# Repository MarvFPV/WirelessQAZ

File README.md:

# WARNING: Unsure if i ever fixed the electrical issues around the charging IC, please sanity check before using

# QAZ-BLE

a 34 key, QAZ style, integrated BLE keyboard.   
Included are PCB files and 3d printable case files.

### PCB
The PCB includes in-switch LED lighting, USB-C, ESD protection and battery protection, enabling the user to install pretty much any Lipo cell that will fit inside the case

### Case
Hardware needed:

* 8x m3x10mm countersinks
* 4x m3x8mm button head

Printing:

* Print from any non-flexible material, i'd recommend to keep the bottom case metal free for RF reasons tho i have no clue how much of an effect that'd have real world
* no real layer height restrictions, make sure that you can print the threads at least decently well
* 4 or more shells are recommended for a better sounding keyboard aswell as stronger threads
* infill does not matter apart from sound

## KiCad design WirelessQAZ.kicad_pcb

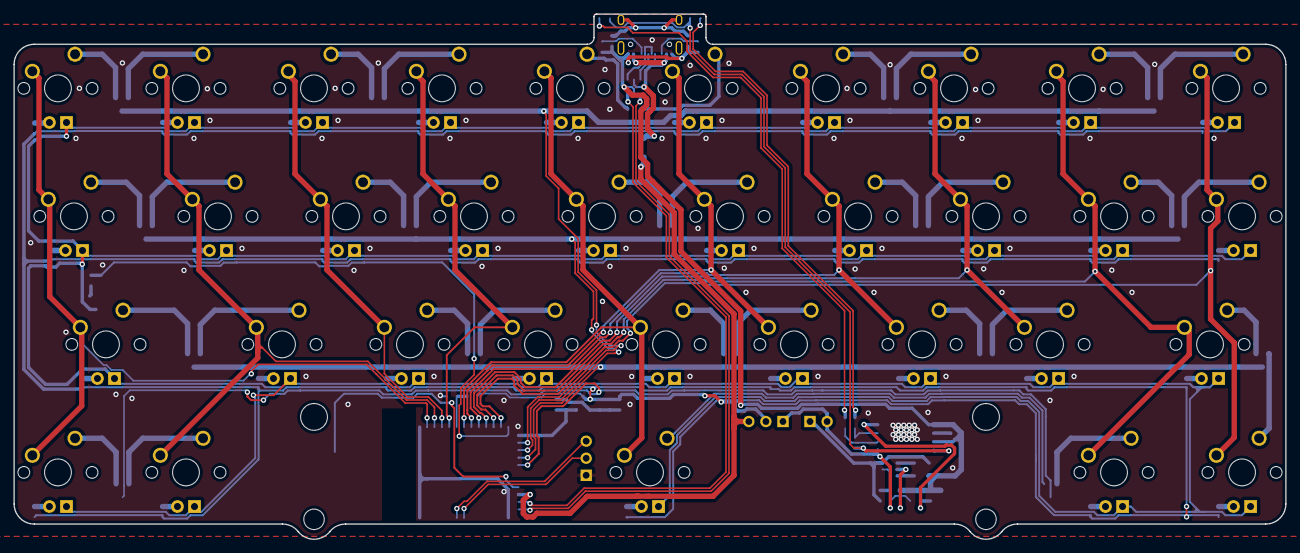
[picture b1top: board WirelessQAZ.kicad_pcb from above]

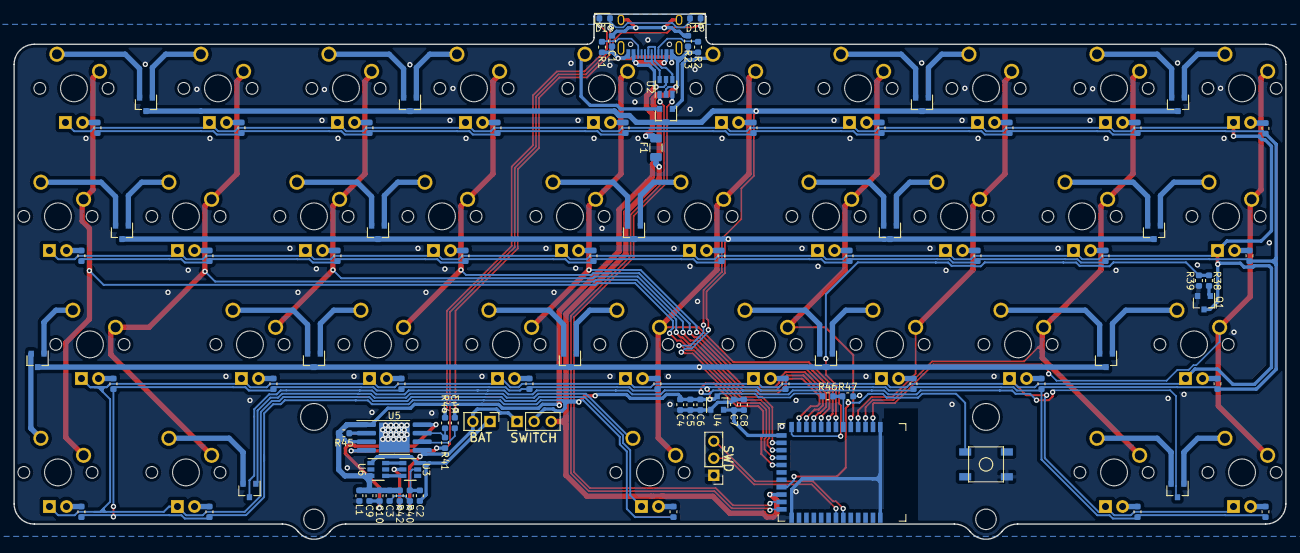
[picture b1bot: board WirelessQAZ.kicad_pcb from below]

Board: 2 copper layers, 189.3 x 78.1 mm, 124 parts (90 on the bottom side), 115 nets.

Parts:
BAT: BATT; PinHeader_1x02_P2.54mm_Vertical
C1, C2, C8, C10: 100nF; C_0603_1608Metric_stealth
C3, C9: 10uF; C_0603_1608Metric_stealth
C4, C5: 4.7uF; C_0603_1608Metric_stealth
C6, C7: 1uF; C_0603_1608Metric_stealth
D1, D2, D3, D4, D5, D6, D7, D8, D9, D10, D11, D12, D13, D14, D15, D16, D17: D_Schottky_x2_KCom_AAK; SOT-23
D18, D19: LED_Small; LED_0603_1608Metric
F1: 500mA; Fuse_1206_3216Metric
L1: PBY160808T-181Y-N; L_0603_1608Metric
MX1, MX2, MX3, MX4, MX5, MX6, MX7, MX8, MX9, MX12, MX13, MX14, MX15, MX16, MX17, MX18, MX19, MX20, MX22, MX23, MX24, MX25, MX26, MX27, MX28, MX30, MX31, MX33, MX34: MX-LED; MXOnly-1U
MX10, MX11: MX-LED; MXOnly-1.25U
MX21: MX-LED; MXOnly-1.75U
MX29: MX-LED; MXOnly-1.5U
MX32: MX-LED; MXOnly-6.25U-ReversedStabilizers
Q1: AO3400A; SOT-23
R1, R2: 5.1k; R_0603_1608Metric_stealth
R3, R4, R5, R6, R7, R8, R9, R10, R11, R12, R13, R14, R15, R16, R17, R18, R19, R20, R21, R22, R24, R25, R26, R27, R28, R29, R30, R31, R32, R33, R34, R35, R36, R37: 680; R_0603_1608Metric_stealth
R23: 1M; R_0603_1608Metric_stealth
R38, R40: 100; R_0603_1608Metric_stealth
R39, R41: 10k; R_0603_1608Metric_stealth
R42: 1k; R_0603_1608Metric_stealth
R43, R44: 2.7k; R_0603_1608Metric_stealth
R45: 1.8k; R_0603_1608Metric_stealth
R46: 1.3M; R_0603_1608Metric_stealth
R47: 2M; R_0603_1608Metric_stealth
SW1: SW_Push; SKQG-1155865
SWD: SWD; PinHeader_1x03_P2.54mm_Vertical
SWITCH: Switch; PinHeader_1x03_P2.54mm_Vertical
U1: nRF52840_holyiot_18010
U2: USBLC6-2SC6; SOT-23-6
U3: DW01A; SOT-23-6
U4: XC6206P332MR; SOT-23
U5: TP4056; SOP-8-1EP_4.57x4.57mm_P1.27mm_EP4.57x4.45mm
U6: FS8205; SOT-23-6
USB1: HRO-TYPE-C-31-M-12; HRO-TYPE-C-31-M-12-Assembly

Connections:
+3V3: C7.1, C8.1, U1.14, U4.2
+5V: C4.1, C5.1, C6.1, R3.2, R4.2, R5.2, R6.2, R7.2, R8.2, R9.2, R10.2, R11.2, R12.2, R13.2, R14.2, R15.2, R16.2, R17.2, R18.2, R19.2, R20.2, R21.2, R22.2, R24.2, R25.2, R26.2, R27.2, R28.2, R29.2, R30.2, R31.2, R32.2, R33.2, R34.2, R35.2, R36.2, R37.2, R46.1, SWITCH.2, U4.3
/5V_USB: F1.1, SWITCH.3, U1.22
/Col0: MX1.1, MX11.1, MX21.1, MX30.1, U1.2
/Col1: MX2.1, MX12.1, MX22.1, MX31.1, U1.3
/Col2: MX3.1, MX13.1, MX23.1, U1.4
/Col3: MX4.1, MX14.1, MX24.1, U1.5
/Col4: MX5.1, MX15.1, MX25.1, MX32.1, U1.7
/Col5: MX6.1, MX16.1, MX26.1, U1.8
/Col6: MX7.1, MX17.1, MX27.1, U1.9
/Col7: MX8.1, MX18.1, MX28.1, U1.10
/Col8: MX9.1, MX19.1, MX29.1, MX33.1, U1.11
/Col9: MX10.1, MX20.1, MX34.1, U1.12
/LED-: MX1.4, MX2.4, MX3.4, MX4.4, MX5.4, MX6.4, MX7.4, MX8.4, MX9.4, MX10.4, MX11.4, MX12.4, MX13.4, MX14.4, MX15.4, MX16.4, MX17.4, MX18.4, MX19.4, MX20.4, MX21.4, MX22.4, MX23.4, MX24.4, MX25.4, MX26.4, MX27.4, MX28.4, MX29.4, MX30.4, MX31.4, MX32.4, MX33.4, MX34.4, Q1.3
/LED_PWM: R38.2, R39.1, U1.13
/MCU_D+: U1.24, U2.1
/MCU_D-: U1.23, U2.3
/RESET: SW1.1, U1.21
/Row0: D1.3, D2.3, D3.3, D4.3, D5.3, U1.15
/Row1: D6.3, D7.3, D8.3, D9.3, D10.3, U1.16
/Row2: D11.3, D12.3, D13.3, D14.3, D15.3, U1.17
/Row3: D16.3, D17.3, U1.18
/USB_D+: U2.6, USB1.6, USB1.8
/USB_D-: U2.4, USB1.5, USB1.7
GND: C4.2, C5.2, C6.2, C7.2, C8.2, L1.1, Q1.2, R39.2, R47.2, SW1.2, SWD.1, U1.1, U1.25, U1.37, U4.1, U5.9
GNDPWR: C1.1, C3.2, C9.2, C10.2, L1.2, R1.1, R2.2, R23.2, R42.2, R45.2, U2.2, U5.1, U5.3, U6.3, USB1.1, USB1.12
unnamed: C1.2, R23.1, USB1.13
unnamed: BAT.1, C2.1, U3.6, U6.1
unnamed: C2.2, R40.1, U3.5
unnamed: BAT.2, C3.1, R40.2, SWITCH.1, U5.5
unnamed: C9.1, C10.1, U5.8
unnamed: D1.1, MX1.2
unnamed: D1.2, MX2.2
unnamed: D2.1, MX3.2
unnamed: D2.2, MX4.2
unnamed: D3.1, MX5.2
unnamed: D3.2, MX6.2
unnamed: D4.1, MX7.2
unnamed: D4.2, MX8.2
unnamed: D5.1, MX9.2
unnamed: D5.2, MX10.2
unnamed: D6.1, MX11.2
unnamed: D6.2, MX12.2
unnamed: D7.1, MX13.2
unnamed: D7.2, MX14.2
unnamed: D8.1, MX15.2
unnamed: D8.2, MX16.2
unnamed: D9.1, MX17.2
unnamed: D9.2, MX18.2
unnamed: D10.1, MX19.2
unnamed: D10.2, MX20.2
unnamed: D11.1, MX21.2
unnamed: D11.2, MX22.2
unnamed: D12.1, MX23.2
unnamed: D12.2, MX24.2
unnamed: D13.1, MX25.2
unnamed: D13.2, MX26.2
unnamed: D14.1, MX27.2
unnamed: D14.2, MX28.2
unnamed: D15.1, MX29.2
unnamed: D15.2, MX34.2
unnamed: D16.1, MX30.2
unnamed: D16.2, MX31.2
unnamed: D17.1, MX32.2
unnamed: D17.2, MX33.2
unnamed: D18.1, R43.1
unnamed: D18.2, D19.2, R41.1, U5.4
unnamed: D19.1, R44.1
unnamed: F1.2, U2.5, USB1.2, USB1.11
unnamed: SWD.2, U1.31
unnamed: SWD.3, U1.32
unnamed: MX1.3, R3.1
unnamed: MX2.3, R4.1
unnamed: MX3.3, R5.1
unnamed: MX4.3, R6.1
unnamed: MX5.3, R7.1
unnamed: MX6.3, R8.1
unnamed: MX7.3, R9.1
unnamed: MX8.3, R10.1
unnamed: MX9.3, R11.1
unnamed: MX10.3, R12.1
unnamed: MX11.3, R13.1
unnamed: MX12.3, R14.1
unnamed: MX13.3, R15.1
unnamed: MX14.3, R16.1
unnamed: MX15.3, R17.1
unnamed: MX16.3, R18.1
unnamed: MX17.3, R19.1
unnamed: MX18.3, R20.1
unnamed: MX19.3, R21.1
unnamed: MX20.3, R22.1
unnamed: MX21.3, R24.1
unnamed: MX22.3, R25.1
unnamed: MX23.3, R26.1
unnamed: MX24.3, R27.1
unnamed: MX25.3, R28.1
unnamed: MX26.3, R29.1
unnamed: MX27.3, R30.1
unnamed: MX28.3, R31.1
unnamed: MX29.3, R32.1
unnamed: MX30.3, R33.1
unnamed: MX31.3, R34.1
unnamed: MX32.3, R35.1
unnamed: MX33.3, R36.1
unnamed: MX34.3, R37.1
unnamed: Q1.1, R38.1
unnamed: R1.2, USB1.10
unnamed: R2.1, USB1.4
unnamed: R41.2, R44.2, U5.7
unnamed: R42.1, U3.2
unnamed: R43.2, U5.6
unnamed: R45.1, U5.2
unnamed: R46.2, R47.1, U1.6
unnamed: U3.1, U6.6
unnamed: U3.3, U6.4

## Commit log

2021-03-02 added files
2021-08-06 things happening
2021-08-07 things
2024-04-22 cleanup
